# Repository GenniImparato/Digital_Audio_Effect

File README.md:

# Digital_Audio_Effect

## Index

* ### [Overview](#intro)
* ### [Videos](#videos)
* ### [Requirements](#req)
  * #### [Hardware](#hw)
  * #### [Software](#sw)
* ### [Getting Started](#get)
* ### [DSP Effects](#dsp)
  * #### [Delay](#delay)
  * #### [Filter](#filter) 
* ### [Future Improvements](#future)

## Overview
This project is a platform to experiment with **real-time DSP effects** on
audio, with an STM32 microprocessor, using a multi-threaded, real-time environment.
The application has been developed on top of the **Miosix** embedded operative system which provided real-time operating system (RTOS) features, as well as a native multi-threaded enviroment.
A full detailed document explaining the project in details can be found at:
https://github.com/GenniImparato/Digital_Audio_Effect/blob/main/docs/report/Digital_Audio_Effects.pdf

## Videos
https://user-images.githubusercontent.com/37338634/153053574-94ea6515-ac46-4c21-b3ac-aa7877b238f6.mp4

https://user-images.githubusercontent.com/37338634/153054718-db798998-3f35-4ed6-b5b4-32b3baa28a30.mp4

https://user-images.githubusercontent.com/37338634/153054537-bed419cf-c9f3-40c2-ad0e-0b04481bedc5.mp4

## Requirements

### Hardware Requirements
- STM32F407 Discovery Board
- Custom PCB (see `hardware` folder for more details)

### Software Requirements
- [Miosix](https://miosix.org/) OS
- [QSTLink2](https://github.com/fpoussin/QStlink2) for board configuration

## Getting started

1. Connect the microcontroller to the PC with the USB cable or with the external power supply of the PCB.

2. Open `QSTLink2` to connect the board through the `connect` command.

3. Open a terminal, go to the `firmware` folder and type `make` to compile the project.

   ```
   cd path/to/project/firmware   
   make
   ```

4. From `QSTLink2`, send the code to the board through the `send` command.

## DSP Effects
The following are the implemented DSP effects, which values can be dinamically modified. 

### Delay
As the name implies, this effect delays the flow of the audio source by a given amount.

### Filter
This effect can be configured as:
- Low-pass filter
- High-pass filter
- Band-pass filter

Each of those modes can be dinamically changed, as well as their values.

## Future Improvements
**[+]** Implementation of more audio effects

**[+]** Anti-aliasing filtering

**[+]** Sine curves visualization

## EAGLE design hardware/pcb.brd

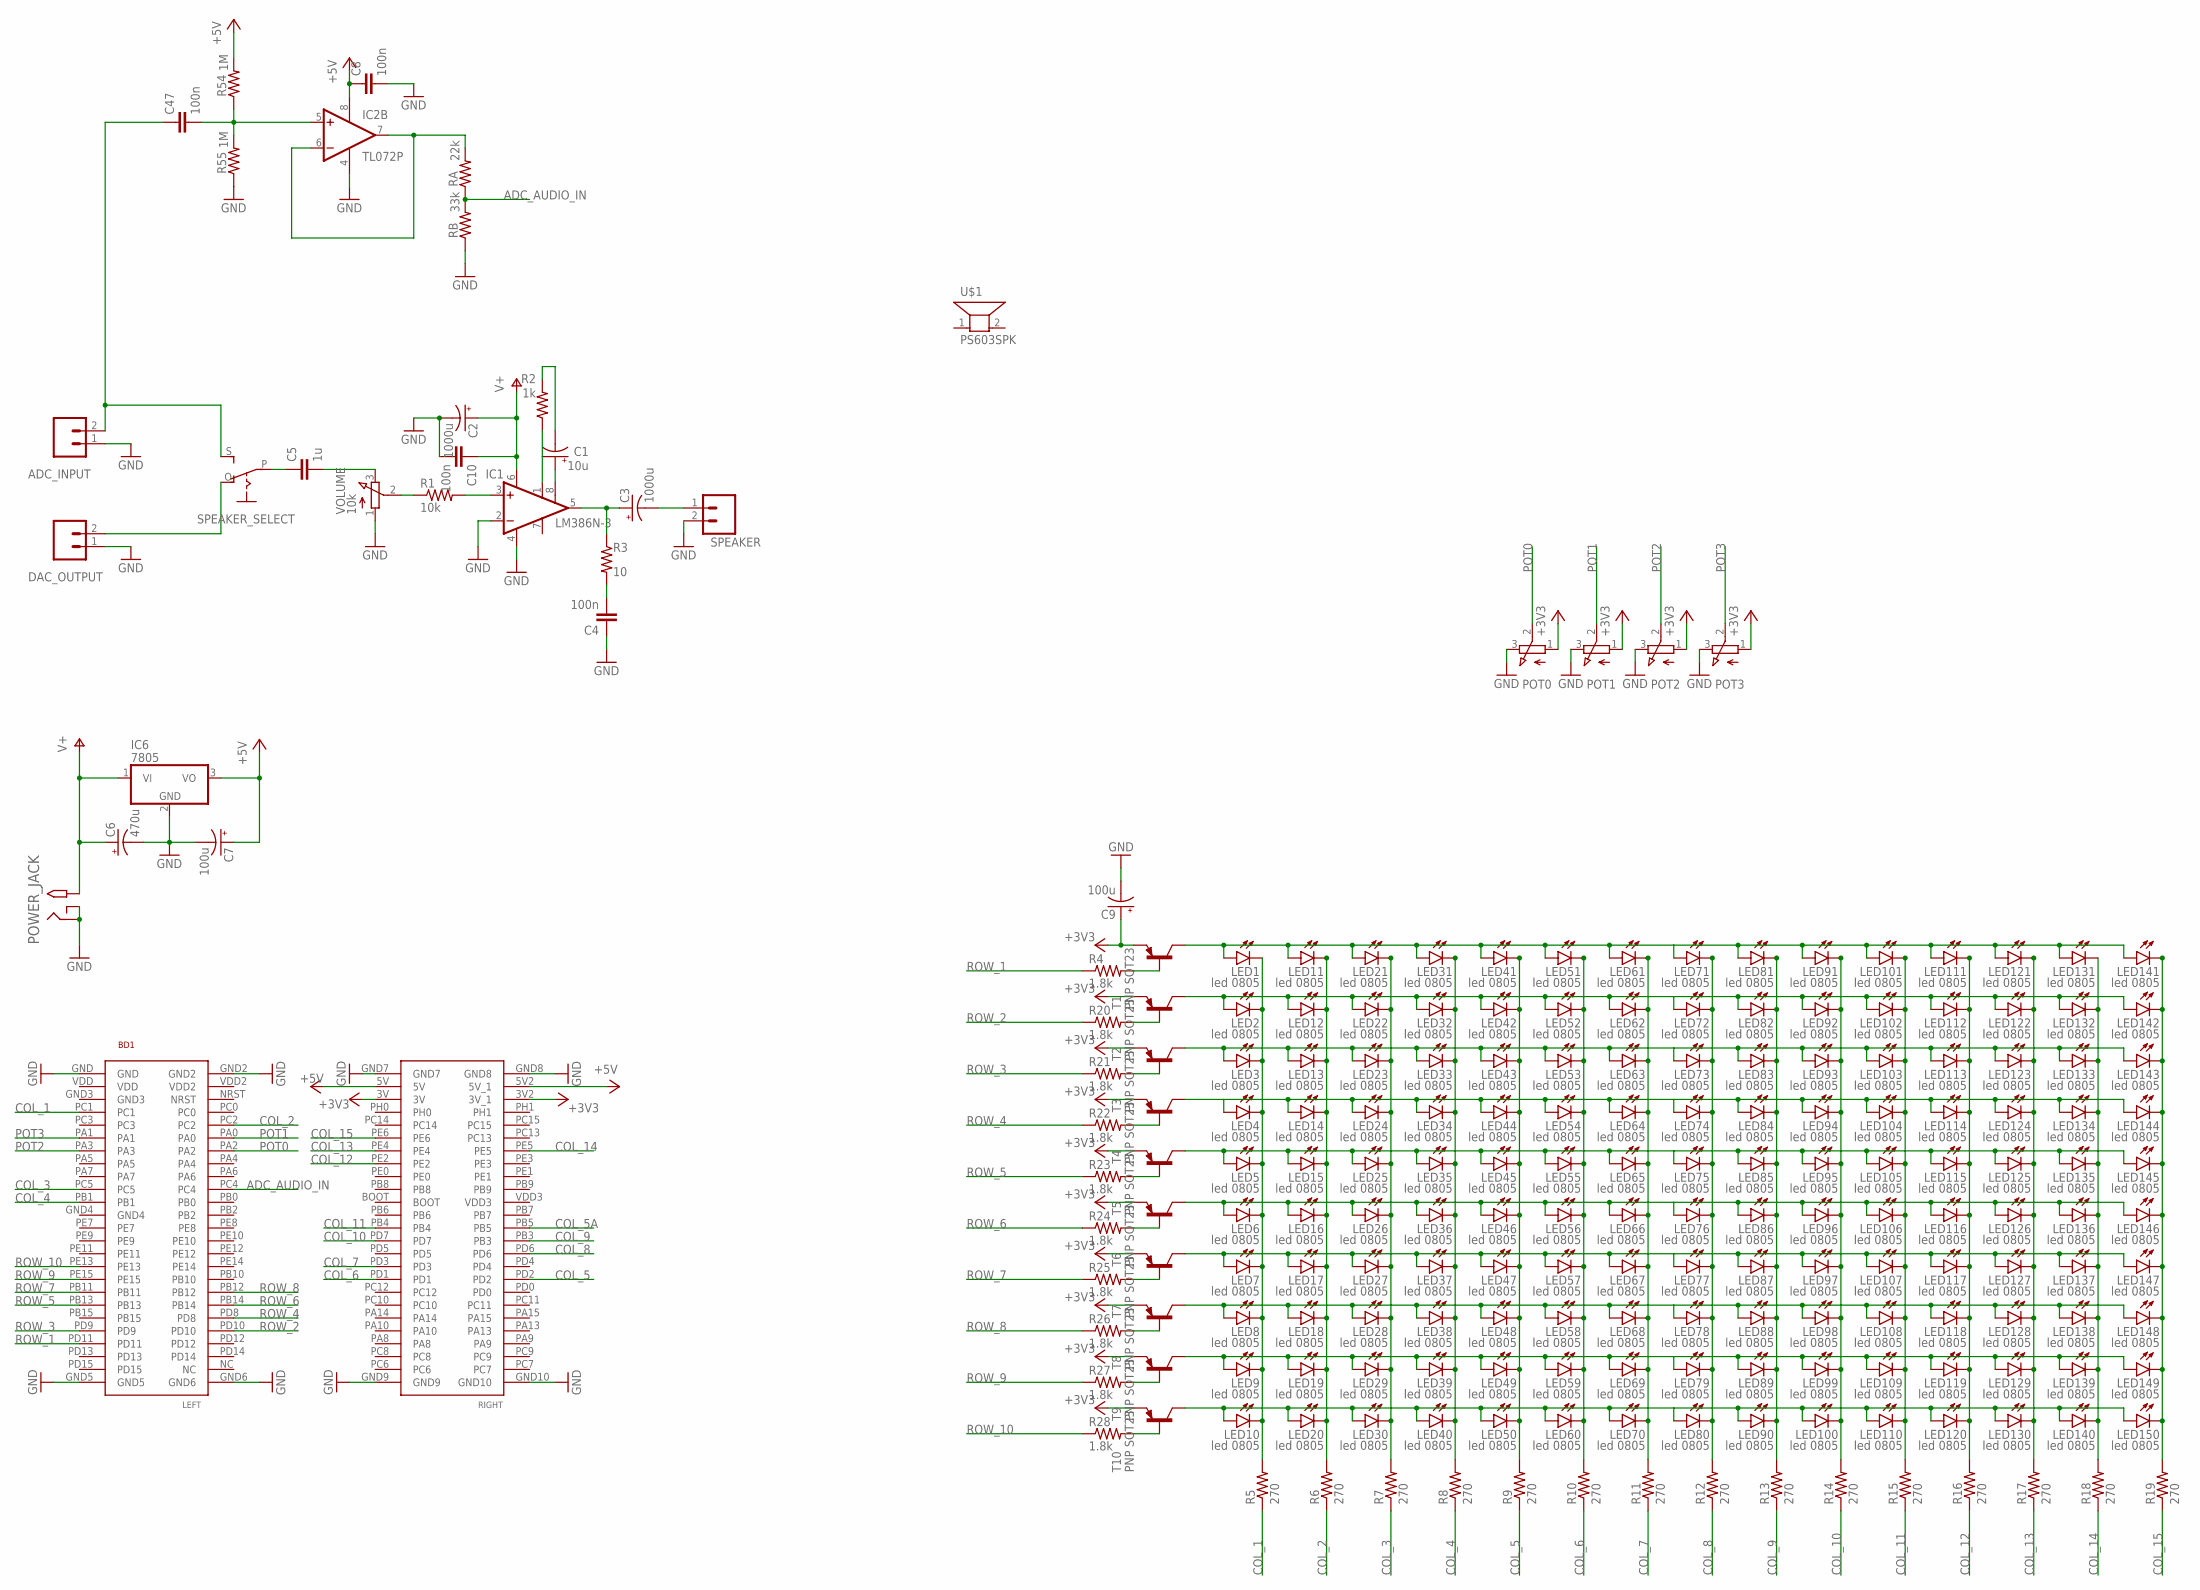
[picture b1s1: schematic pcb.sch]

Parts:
ADC_INPUT: M02; 02P
BD1: STM32F4-DISCOVERY; STM32F407VG
C1: 10u; E5-6
C2, C3: 1000u; E5-13
C4, C47: 100n; C5B3.5
C5: 1u; C050-035X075
C6: 470u; E5-6
C7, C9: 100u; E5-6
C8, C10: 100n; C0805
DAC_OUTPUT: M02; 02P
IC1: LM386N-3; DIL08
IC2: TL072P; DIL08
IC6: 7805; TO220H
LED1, LED2, LED3, LED4, LED5, LED6, LED7, LED8, LED9, LED10, LED11, LED12, LED13, LED14, LED15, LED16, LED17, LED18, LED19, LED20, LED21, LED22, LED23, LED24, LED25, LED26, LED27, LED28, LED29, LED30, LED31, LED32, LED33, LED34, LED35, LED36, LED37, LED38, LED39, LED40, LED41, LED42, LED43, LED44, LED45, LED46, LED47, LED48, LED49, LED50, LED51, LED52, LED53, LED54, LED55, LED56, LED57, LED58, LED59, LED60, LED61, LED62, LED63, LED64, LED65, LED66, LED67, LED68, LED69, LED70, LED71, LED72, LED73, LED74, LED75, LED76, LED77, LED78, LED79, LED80, LED81, LED82, LED83, LED84, LED85, LED86, LED87, LED88, LED89, LED90, LED91, LED92, LED93, LED94, LED95, LED96, LED97, LED98, LED99, LED100, LED101, LED102, LED103, LED104, LED105, LED106, LED107, LED108, LED109, LED110, LED111, LED112, LED113, LED114, LED115, LED116, LED117, LED118, LED119, LED120, LED121, LED122, LED123, LED124, LED125, LED126, LED127, LED128, LED129, LED130, LED131, LED132, LED133, LED134, LED135, LED136, LED137, LED138, LED139, LED140, LED141, LED142, LED143, LED144, LED145, LED146, LED147, LED148, LED149, LED150: led 0805; CHIPLED_0805
POT0, POT1, POT2, POT3: 3RP/1610N
POWER_JACK: 2.1MMJACKTHM; PJ-102A
R1: 10k; 0207/10
R2: 1k; 0207/10
R3: 10; 0207/10
R4, R20, R21, R22, R23, R24, R25, R26, R27, R28: 1.8k; R0805
R5, R6, R7, R8, R9, R10, R11, R12, R13, R14, R15, R16, R17, R18, R19: 270; R0805
R54, R55: 1M; 0207/10
RA: 22k; 0207/10
RB: 33k; 0207/10
SPEAKER: M02; 02P
SPEAKER_SELECT: EG1218S; EG1218
T1, T2, T3, T4, T5, T6, T7, T8, T9, T10: PNP SOT23; SOT23-BEC
U$1: PS603SPK; PS603
VOLUME: 10k; 3RP/1610N

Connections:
+3V3: BD1.3V, BD1.3V2 (3V_1), C9.+, POT0.1 (A), POT1.1 (A), POT2.1 (A), POT3.1 (A), T1.E, T2.E, T3.E, T4.E, T5.E, T6.E, T7.E, T8.E, T9.E, T10.E
+5V: BD1.5V, BD1.5V2 (5V_1), C7.+, C8.1, IC2.8 (V+), IC6.3 (VO), R54.2
ADC_AUDIO_IN: BD1.PC4, RA.1, RB.2
COL_1: BD1.PC1, R5.1
COL_2: BD1.PC2, R6.1
COL_3: BD1.PC5, R7.1
COL_4: BD1.PB1, R8.1
COL_5: BD1.PD2, R9.1
COL_5A: BD1.PB5
COL_6: BD1.PD1, R10.1
COL_7: BD1.PD3, R11.1
COL_8: BD1.PD6, R12.1
COL_9: BD1.PB3, R13.1
COL_10: BD1.PD7, R14.1
COL_11: BD1.PB4, R15.1
COL_12: BD1.PE2, R16.1
COL_13: BD1.PE4, R17.1
COL_14: BD1.PE5, R18.1
COL_15: BD1.PE6, R19.1
GND: ADC_INPUT.1, BD1.GND, BD1.GND2, BD1.GND5, BD1.GND6, BD1.GND7, BD1.GND8, BD1.GND9, BD1.GND10, C2.-, C4.1, C6.-, C7.-, C8.2, C9.-, C10.2, DAC_OUTPUT.1, IC1.2 (-IN), IC1.4 (GND), IC2.4 (V-), IC6.2 (GND), POT0.3 (E), POT1.3 (E), POT2.3 (E), POT3.3 (E), POWER_JACK.RING, POWER_JACK.RING_SW, R55.1, RB.1, SPEAKER.2, VOLUME.1 (A)
GUITAR_BUFFER: IC2.6 (-IN), IC2.7 (OUT), RA.2
unnamed: LED1.C, LED2.C, LED3.C, LED4.C, LED5.C, LED6.C, LED7.C, LED8.C, LED9.C, LED10.C, R5.2
unnamed: C5.2, VOLUME.3 (E)
unnamed: LED11.C, LED12.C, LED13.C, LED14.C, LED15.C, LED16.C, LED17.C, LED18.C, LED19.C, LED20.C, R6.2
unnamed: LED21.C, LED22.C, LED23.C, LED24.C, LED25.C, LED26.C, LED27.C, LED28.C, LED29.C, LED30.C, R7.2
unnamed: LED31.C, LED32.C, LED33.C, LED34.C, LED35.C, LED36.C, LED37.C, LED38.C, LED39.C, LED40.C, R8.2
unnamed: LED41.C, LED42.C, LED43.C, LED44.C, LED45.C, LED46.C, LED47.C, LED48.C, LED49.C, LED50.C, R9.2
unnamed: LED51.C, LED52.C, LED53.C, LED54.C, LED55.C, LED56.C, LED57.C, LED58.C, LED59.C, LED60.C, R10.2
unnamed: LED61.C, LED62.C, LED63.C, LED64.C, LED65.C, LED66.C, LED67.C, LED68.C, LED69.C, LED70.C, R11.2
unnamed: LED71.C, LED72.C, LED73.C, LED74.C, LED75.C, LED76.C, LED77.C, LED78.C, LED79.C, LED80.C, R12.2
unnamed: LED81.C, LED82.C, LED83.C, LED84.C, LED85.C, LED86.C, LED87.C, LED88.C, LED89.C, LED90.C, R13.2
unnamed: LED91.C, LED92.C, LED93.C, LED94.C, LED95.C, LED96.C, LED97.C, LED98.C, LED99.C, LED100.C, R14.2
unnamed: LED101.C, LED102.C, LED103.C, LED104.C, LED105.C, LED106.C, LED107.C, LED108.C, LED109.C, LED110.C, R15.2
unnamed: LED111.C, LED112.C, LED113.C, LED114.C, LED115.C, LED116.C, LED117.C, LED118.C, LED119.C, LED120.C, R16.2
unnamed: LED121.C, LED122.C, LED123.C, LED124.C, LED125.C, LED126.C, LED127.C, LED128.C, LED129.C, LED130.C, R17.2
unnamed: LED131.C, LED132.C, LED133.C, LED134.C, LED135.C, LED136.C, LED137.C, LED138.C, LED139.C, LED140.C, R18.2
unnamed: LED141.C, LED142.C, LED143.C, LED144.C, LED145.C, LED146.C, LED147.C, LED148.C, LED149.C, LED150.C, R19.2
unnamed: LED1.A, LED11.A, LED21.A, LED31.A, LED41.A, LED51.A, LED61.A, LED71.A, LED81.A, LED91.A, LED101.A, LED111.A, LED121.A, LED131.A, LED141.A, T1.C
unnamed: R25.2, T7.B
unnamed: R26.2, T8.B
unnamed: LED7.A, LED17.A, LED27.A, LED37.A, LED47.A, LED57.A, LED67.A, LED77.A, LED87.A, LED97.A, LED107.A, LED117.A, LED127.A, LED137.A, LED147.A, T7.C
unnamed: LED8.A, LED18.A, LED28.A, LED38.A, LED48.A, LED58.A, LED68.A, LED78.A, LED88.A, LED98.A, LED108.A, LED118.A, LED128.A, LED138.A, LED148.A, T8.C
unnamed: LED9.A, LED19.A, LED29.A, LED39.A, LED49.A, LED59.A, LED69.A, LED79.A, LED89.A, LED99.A, LED109.A, LED119.A, LED129.A, LED139.A, LED149.A, T9.C
unnamed: LED10.A, LED20.A, LED30.A, LED40.A, LED50.A, LED60.A, LED70.A, LED80.A, LED90.A, LED100.A, LED110.A, LED120.A, LED130.A, LED140.A, LED150.A, T10.C
unnamed: ADC_INPUT.2, C47.1, SPEAKER_SELECT.S
unnamed: DAC_OUTPUT.2, SPEAKER_SELECT.O
unnamed: R1.1, VOLUME.2 (S)
unnamed: IC1.3 (+IN), R1.2
unnamed: C1.+, IC1.8 (GAIN)
unnamed: IC1.1 (GAIN), R2.1
unnamed: C1.-, R2.2
unnamed: C3.+, IC1.5 (OUT), R3.1
unnamed: C3.-, SPEAKER.1
unnamed: C4.2, R3.2
unnamed: C5.1, SPEAKER_SELECT.P
unnamed: R4.2, T1.B
unnamed: LED2.A, LED12.A, LED22.A, LED32.A, LED42.A, LED52.A, LED62.A, LED72.A, LED82.A, LED92.A, LED102.A, LED112.A, LED122.A, LED132.A, LED142.A, T2.C
unnamed: R20.2, T2.B
unnamed: LED3.A, LED13.A, LED23.A, LED33.A, LED43.A, LED53.A, LED63.A, LED73.A, LED83.A, LED93.A, LED103.A, LED113.A, LED123.A, LED133.A, LED143.A, T3.C
unnamed: R21.2, T3.B
unnamed: LED4.A, LED14.A, LED24.A, LED34.A, LED44.A, LED54.A, LED64.A, LED74.A, LED84.A, LED94.A, LED104.A, LED114.A, LED124.A, LED134.A, LED144.A, T4.C
unnamed: R22.2, T4.B
unnamed: LED5.A, LED15.A, LED25.A, LED35.A, LED45.A, LED55.A, LED65.A, LED75.A, LED85.A, LED95.A, LED105.A, LED115.A, LED125.A, LED135.A, LED145.A, T5.C
unnamed: R23.2, T5.B
unnamed: LED6.A, LED16.A, LED26.A, LED36.A, LED46.A, LED56.A, LED66.A, LED76.A, LED86.A, LED96.A, LED106.A, LED116.A, LED126.A, LED136.A, LED146.A, T6.C
unnamed: R24.2, T6.B
unnamed: R27.2, T9.B
unnamed: R28.2, T10.B
unnamed: C47.2, IC2.5 (+IN), R54.1, R55.2
POT0: BD1.PA2, POT0.2 (S)
POT1: BD1.PA0, POT1.2 (S)
POT2: BD1.PA3, POT2.2 (S)
POT3: BD1.PA1, POT3.2 (S)
ROW_1: BD1.PD11, R4.1
ROW_2: BD1.PD10, R20.1
ROW_3: BD1.PD9, R21.1
ROW_4: BD1.PD8, R22.1
ROW_5: BD1.PB13, R23.1
ROW_6: BD1.PB14, R24.1
ROW_7: BD1.PB11, R25.1
ROW_8: BD1.PB12, R26.1
ROW_9: BD1.PE15, R27.1
ROW_10: BD1.PE13, R28.1
V+: C2.+, C6.+, C10.1, IC1.6 (VS), IC6.1 (VI), POWER_JACK.TIP

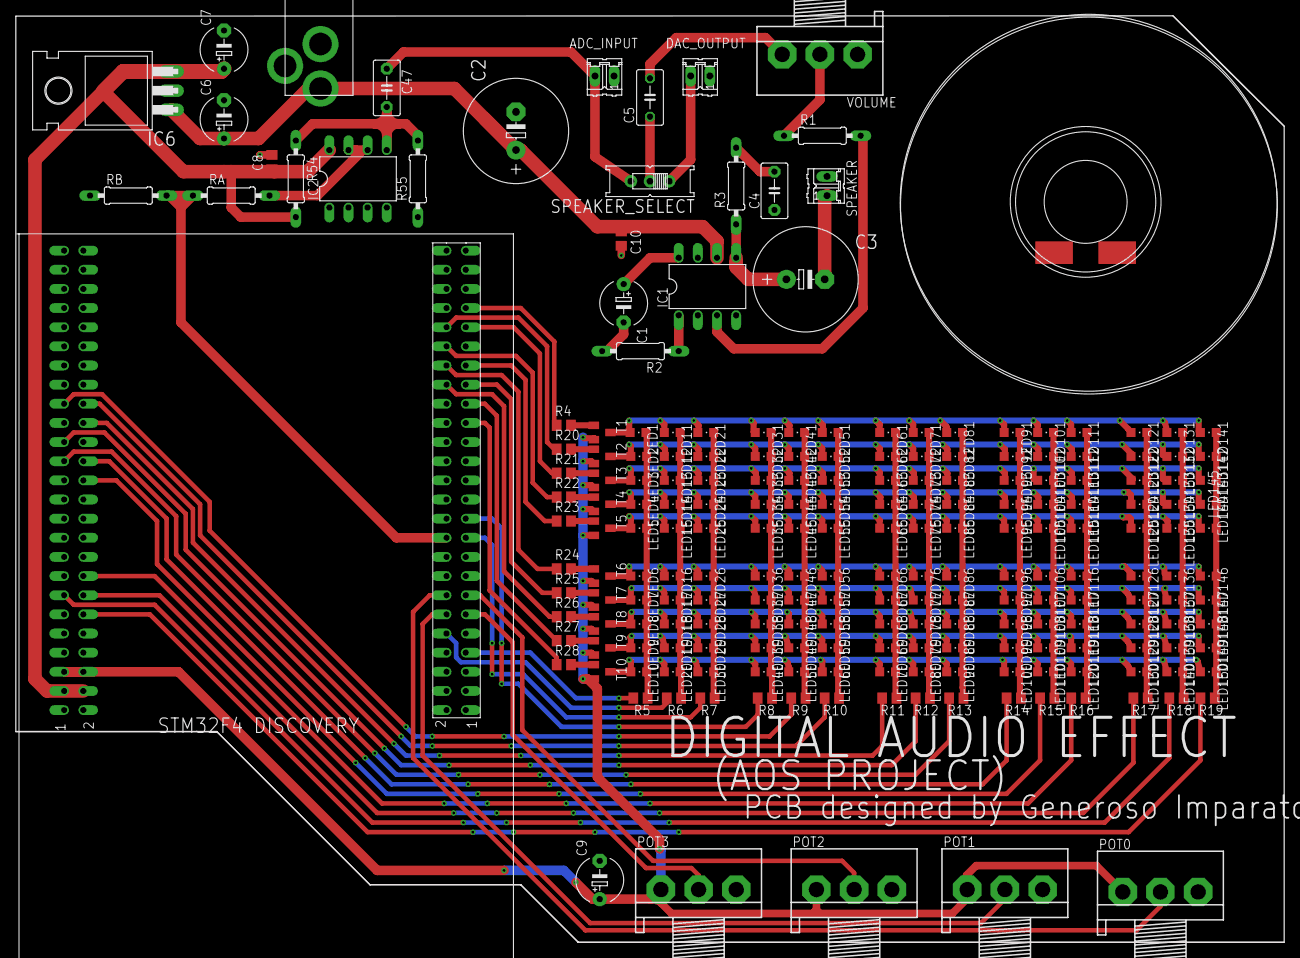
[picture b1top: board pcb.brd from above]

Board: 2 copper layers, 168.3 x 122.9 mm, 218 parts (0 on the bottom side), 83 nets.

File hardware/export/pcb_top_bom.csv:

Comment,Designator,Footprint,LCSC Part #
1.8k,R4 R20 R21 R22 R23 R24 R25 R26 R27 R28,R0805,
100n,C8 C10,C0805,
270,R5 R6 R7 R8 R9 R10 R11 R12 R13 R14 R15 R16 R17 R18 R19,R0805,
PNP SOT23,T1 T2 T3 T4 T5 T6 T7 T8 T9 T10,SOT23-BEC,
led 0805,LED1 LED2 LED3 LED4 LED5 LED6 LED7 LED8 LED9 LED10 LED11 LED12 LED13 LED14 LED15 LED16 LED17 LED18 LED19 LED20 LED21 LED22 LED23 LED24 LED25 LED26 LED27 LED28 LED29 LED30 LED31 LED32 LED33 LED34 LED35 LED36 LED37 LED38 LED39 LED40 LED41 LED42 LED43 LED44 LED45 LED46 LED47 LED48 LED49 LED50 LED51 LED52 LED53 LED54 LED55 LED56 LED57 LED58 LED59 LED60 LED61 LED62 LED63 LED64 LED65 LED66 LED67 LED68 LED69 LED70 LED71 LED72 LED73 LED74 LED75 LED76 LED77 LED78 LED79 LED80 LED81 LED82 LED83 LED84 LED85 LED86 LED87 LED88 LED89 LED90 LED91 LED92 LED93 LED94 LED95 LED96 LED97 LED98 LED99 LED100 LED101 LED102 LED103 LED104 LED105 LED106 LED107 LED108 LED109 LED110 LED111 LED112 LED113 LED114 LED115 LED116 LED117 LED118 LED119 LED120 LED121 LED122 LED123 LED124 LED125 LED126 LED127 LED128 LED129 LED130 LED131 LED132 LED133 LED134 LED135 LED136 LED137 LED138 LED139 LED140 LED141 LED142 LED143 LED144 LED145 LED146 LED147 LED148 LED149 LED150,CHIPLED_0805,

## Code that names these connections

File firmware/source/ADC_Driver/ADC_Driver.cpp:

#include "ADC_Driver.h"

using namespace miosix;

const unsigned short    ADC_Driver::potChannels[POTS_COUNT] = {2,8,3,1};

AudioBufferQueue*       ADC_Driver::dmaBuffer;
miosix::Thread*         ADC_Driver::waitingThread;
miosix::Thread*         ADC_Driver::restartThread;
bool                    ADC_Driver::dmaRefillWaiting = false;

unsigned short ADC_Driver::buffer[AUDIO_BUFFERS_SIZE];


typedef Gpio<GPIOA_BASE,2> pot0;
typedef Gpio<GPIOB_BASE,0> pot1;
typedef Gpio<GPIOA_BASE,3> pot2;
typedef Gpio<GPIOA_BASE,1> pot3;
typedef Gpio<GPIOC_BASE,4> audioInput;


void ADC_Driver::init()
{
    dmaBuffer = new AudioBufferQueue();

    pot0::mode(Mode::INPUT_ANALOG);
    pot1::mode(Mode::INPUT_ANALOG);
    pot2::mode(Mode::INPUT_ANALOG);
    pot3::mode(Mode::INPUT_ANALOG);
    audioInput::mode(Mode::INPUT_ANALOG);

    {
        FastInterruptDisableLock dLock;
        //Enable DMA2 clock
        RCC->AHB1ENR |= RCC_AHB1ENR_DMA2EN;
        RCC_SYNC();
    }
	//enable ADC1 clock
	RCC->APB2ENR |= RCC_APB2ENR_ADC1EN;
    RCC_SYNC();

    ADC->CCR |= (1<<16)|(1<<17);

   	//activate ADC1
    ADC1->CR2 = ADC_CR2_ADON;

    configureADC2();

    //wait
    miosix::delayMs(500);

    NVIC_SetPriority(DMA2_Stream2_IRQn,2);//High priority for DMA
    NVIC_EnableIRQ(DMA2_Stream2_IRQn);

    dmaRestart();

    /*unsigned short *buff;
    unsigned int size;
    dmaBuffer->tryGetWritableBuffer(buff);
   
    for(int i=0; i<AUDIO_BUFFERS_SIZE; i++)
    {
        buff[i] = i*60000/AUDIO_BUFFERS_SIZE;
    }
    dmaBuffer->bufferFilled(AUDIO_BUFFERS_SIZE);*/

    configureTIM2();

    restartThread = Thread::create(&ADC_Driver::threadMain, 256, 0);
}

void ADC_Driver::configureTIM2(void)
{
    // enable TIM2 clock (bit0)
    RCC->APB1ENR |= (1 << 0);           

    //44.1 Khz
    TIM2->PSC = 16;
    TIM2->ARR = 55;

    /* Reset the MMS Bits */
    TIM2->CR2 &= (uint16_t)~TIM_CR2_MMS;
    /* Select the TRGO source */
    TIM2->CR2 |=  TIM_CR2_MMS_1; //UPDATE EVENT       

    // Update Interrupt Enable
    //TIM2->DIER |= (1 << 0);

    // enable TIM2 IRQ from NVIC
    //NVIC_EnableIRQ(TIM2_IRQn);

    // Enable Timer 2 module (CEN, bit0)
    TIM2->CR1 |= (1 << 0);
}

void ADC_Driver::configureADC2()
{
    RCC->APB2ENR|=RCC_APB2ENR_ADC2EN;  //ADC2 clock enable
    RCC_SYNC();
    ADC2->SQR1&=~ADC_SQR1_L;                         
        
    //set number of conversions per sequence to 1
    ADC2->SQR3&=~ADC_SQR3_SQ1;                   
        
    //clear channel select bits
    ADC2->SQR3|=14;         //set channel
    ADC2->CR1 &= ~ADC_CR1_SCAN; //SCAN mode disabled    
    ADC2->CR2 &= ~ADC_CR2_CONT; //Disable continuous conversion
                    
    ADC1->SMPR1 =   0xFFFFFFFF;
    ADC1->SMPR2 =   0xFFFFFFFF; 
    
    //Trigger on Rising edge
    ADC2->CR2 &=  ~(1<<29);
    ADC2->CR2 |= (1<<28);   
    
    //External Event TIM2 TRGO [0110]
    const uint32_t TIM2_TRGO = ADC_CR2_EXTSEL_2 | ADC_CR2_EXTSEL_1; 
    ADC2->CR2 &= ~(ADC_CR2_EXTSEL);   // remove all selections
    ADC2->CR2 |= TIM2_TRGO;
    
    ADC2->CR2|=ADC_CR2_ADON;
 
    //enable DMA
    ADC2->CR2 |= ADC_CR2_DMA;  

    //starts ADC    
    ADC2->CR2|=ADC_CR2_SWSTART;     
}

//performs a single conversion (uses ADC1)
unsigned short ADC_Driver::singleConversion(unsigned short channel)
{
	//single conversion mode
	ADC1->CR1 = 0;

	//select sample time
    ADC1->SMPR1 =   0xFFFFFFFF;
    ADC1->SMPR2 = 	0xFFFFFFFF; //239.5 cycles sample time

    //select number of converions
    ADC1->SQR1 = 0; 		//single conversion

    //select channel
    ADC1->SQR2 = 0;
    ADC1->SQR3 = channel; 		//channel 1

    //start conversion
    ADC1->CR2 |= ADC_CR2_SWSTART;

    //wait for conversion to end
    while((ADC1->SR & ADC_SR_EOC)==0);

    unsigned int result=ADC1->DR;

    return result;
}

unsigned short ADC_Driver::filterConversions(unsigned short channel)
{
    unsigned int filteredValue;

    static ADCFilter<FILTER_SAMLPLES_COUNT> filter;
    for(int i=0; i<FILTER_SAMLPLES_COUNT; i++)
        filteredValue = filter(singleConversion(channel));

    return filteredValue;
}

unsigned short ADC_Driver::filterConversionsPot(unsigned short pot)
{
	if(pot>=POTS_COUNT)
		return 0;

    return filterConversions(potChannels[pot]);
}

/**
 * Waits until a buffer is available for reading
 * \return a readable buffer from dmaBuffer
 */
const unsigned short * ADC_Driver::getReadableBuffer(miosix::Thread* readerThread)
{
    FastInterruptDisableLock dLock;
    waitingThread = readerThread;
    const unsigned short *result;
    unsigned int size;
    while(dmaBuffer->tryGetReadableBuffer(result, size)==false)
    {
        waitingThread->IRQwait();
        {
            FastInterruptEnableLock eLock(dLock);
            Thread::yield();
        }
    }
    return result;
}

//Configure the DMA to do another transfer
bool ADC_Driver::IRQdmaRestart()
{
    unsigned short* buffer;

    DMA2_Stream2->CR = 0;
    DMA2_Stream2->PAR=reinterpret_cast<unsigned int>(&ADC2->DR); 


    if(!dmaBuffer->tryGetWritableBuffer(buffer))
    {   
        dmaRefillWaiting = true;
        //miosix::ledOn();
        return false;
    }
    else    
        DMA2_Stream2->M0AR=reinterpret_cast<unsigned int>(buffer);

    DMA2_Stream2->NDTR=AUDIO_BUFFERS_SIZE;
    DMA2_Stream2->CR=DMA_SxCR_PL_1    | //High priority DMA stream
                     DMA_SxCR_MSIZE_0 | //Read  16bit at a time from ADC2
                     DMA_SxCR_PSIZE_0 | //Write 16bit at a time to RAM
                     DMA_SxCR_MINC    | //Increment RAM pointer
                     DMA_SxCR_TCIE    | //Interrupt on completion
                     DMA_SxCR_CHSEL_0 | //Select channel 1
                     DMA_SxCR_EN;       //Start the DMA

    return true;
}

void ADC_Driver::bufferEmptied()
{
    FastInterruptDisableLock dLock;
    dmaBuffer->bufferEmptied();
}


//Helper function used to start a DMA transfer from non-interrupt code
bool ADC_Driver::dmaRestart()
{
    FastInterruptDisableLock dLock;
    return IRQdmaRestart();
}

void ADC_Driver::adc2Restart()
{
    ADC2->SR &= ~(ADC_SR_OVR);
    ADC2->CR2 |= (ADC_CR2_DMA|ADC_CR2_DDS);
    //clear the overload
    ADC2->SR &= ~(ADC_SR_OVR|ADC_SR_STRT);
    //start the ADC
    ADC2->CR2 |= (uint32_t)ADC_CR2_SWSTART;
}

//DMA end of transer interrupt handler
void ADC_Driver::IRQdmaEndHandler()
{
    DMA2->LIFCR=DMA_LIFCR_CTCIF2  |
                DMA_LIFCR_CTEIF2  |
                DMA_LIFCR_CDMEIF2 |
                DMA_LIFCR_CFEIF2;

    dmaBuffer->bufferFilled(AUDIO_BUFFERS_SIZE);

    ADC2->CR2 &= ~(ADC_CR2_DDS|ADC_CR2_DMA);

    //dmaBuffer->bufferEmptied();

    if(IRQdmaRestart())
    {
        adc2Restart();

        waitingThread->IRQwakeup();
        if(waitingThread->IRQgetPriority()>Thread::IRQgetCurrentThread()->IRQgetPriority())
            Scheduler::IRQfindNextThread();
    }

    //dmaBuffer->bufferEmptied();

}

void ADC_Driver::threadMain(void *param)
{
    while(true)
    {
        if(dmaRefillWaiting)
        {
            dmaRefillWaiting = false;
            //miosix::ledOff();
            dmaRestart();
            adc2Restart();
        }
        miosix::Thread::yield();
    }
}

void ADC_Driver::IRQTIM2Handler(void)
{  
    // clear interrupt status
    if (TIM2->DIER & 0x01) 
    {
        if (TIM2->SR & 0x01) 
        {
            TIM2->SR &= ~(1U << 0);
        }
    }

    /*static bool ledState = false;
    static int count = 0;

    if(count >= 44100)
    {
        count = 0;
        ledState = !ledState;
    }
    else
        count++;

    ledState = !ledState;

    if(ledState)
        miosix::ledOn();
    else
        miosix::ledOff();*/
}

/**
 * DMA end of transfer interrupt
 */
void __attribute__((naked)) DMA2_Stream2_IRQHandler()
{
    saveContext();
    asm volatile("bl _Z24DMA2_Stream2_IRQHandler_v");
    restoreContext();
}

/**
 * DMA end of transfer interrupt actual implementation
 */
void __attribute__((used)) DMA2_Stream2_IRQHandler_()
{
    ADC_Driver::IRQdmaEndHandler();
}

/**
 * Timer 2 interrupt
 */
void __attribute__((naked)) TIM2_IRQHandler()
{
    saveContext();
    asm volatile("bl _Z16TIM2_IRQHandler_v");
    restoreContext();
}

/**
 * Timer 2 interrupt actual implementation
 */
void __attribute__((used)) TIM2_IRQHandler_()
{
    ADC_Driver::IRQTIM2Handler();
}

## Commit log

2021-03-20 FIRST WORKING COMMIT
    Firmware:
    -miosix working
    -ADC driver working (single conversion)
    Hardware:
    -PCB quasi finita
2021-03-24 DAC_Driver added
2021-03-25 PCB final (in production)
2021-03-26 added AudioEffect
    test with simple wave and tremolo
2021-03-27 added AudioEffect base class and multithreading
2021-03-27 reworked AudioEffect and added/test thread termination
2021-03-28 added working wavetable syntheziser
2021-03-28 reworked Oscillator
2021-03-29 work on synth
2021-04-08 removed AudioEffect thread start in constructor
    bug after repower
2021-04-15 works on synth + added pot thread
2021-04-15 first trial on matrix led
2021-04-16 start class for led matrix
2021-04-17 Basic configuration of Led Matrix
2021-04-17 Added support files for Led Matrix
2021-04-17 Bug Fixing
2021-04-26 deleted DAC_Driver thread
2021-04-27 Buffer implementation for Led Matrix
2021-04-27 Optimizations on buffer and leds behaviour
2021-04-28 added ADC sampling
2021-04-29 Writable strings on Led Matrix
2021-04-30 added audio sources/effect selection
2021-04-30 added Delay effect
2021-05-01 potentiometer selection for synth parameters
2021-05-01 synth pattern
    tab converted to spaces
2021-05-02 Led Matrix Optimizations
2021-05-02 Minor fixes
2021-05-02 converted DSP buffers to float
2021-05-03 controls printed on matrix + adc filter
2021-05-03 moved ADC filter to another file
2021-05-07 Implemented Interrupt Routine for Led Matrix
2021-05-07 Fixed Interrupt disable and removed thread
2021-05-07 fixed random problem on restart + deleted old thread variables
2021-05-10 added button to switch effects/sources
2021-05-11 Implementation of setLeds | Minor changes
2021-05-11 fixed mutex crash + pot loop changes
2021-08-30 bug fixes + optimizations + added FIlter
2021-09-03 small changes
2021-09-03 fixed ADC audio problem
2021-09-06 stable version (maybe)
2021-09-08 minor changes
2021-09-14 Added Report

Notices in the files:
README.md:
GPL license
